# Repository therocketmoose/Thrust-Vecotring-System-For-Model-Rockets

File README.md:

Thrust Vectoring & Landing Control System for Model Rockets

Lead Engineer: Xavier Vimard
Project Start: 27/09/2025
Expected Completion: 20/05/2026

Project Overview:

This repository contains the full development of a thrust-controlled landing system (TCLS) for a model rocket platform. The project aims to design, build, and test a reusable model rocket capable of performing controlled ascent, attitude stabilization, descent management, and soft landing. The objective is to create a working proof-of-concept that integrates thrust vectoring, aerodynamic control, reaction wheel stabilization, and deployable landing legs into a unified flight system. This project is expected to operate over a one-year development window, with several intermediate prototypes and test campaigns.

The rocket platform itself is not the primary focus, the emphasis is the TCLS hardware, control algorithms, and validation testing necessary to achieve reliable vertical landing.

Project Goals:
- Develop a fully functional thrust vectoring system capable of four-axis gimbal control for ascent and landing.

- Implement a stability assist system using grid fins to manage minor deviations during ascent.

- Design a reaction wheel to counter roll and maintain thrust vector orientation.
as roll stabilization is critical, as uncontrolled roll makes TVC ineffective.

- Engineer deployable landing legs to ensure stable recovery after touchdown.

- Build a complete electronics and software stack integrating sensors, control logic, and closed-loop PID stabilization.

- Validate feasibility via simulation, static fire testing, and full-scale launch tests.

Development Timeline:

My project follows a structured month-by-month roadmap:

- Nov 2025: Design, print and stress test the TVC mount, the reaction wheel and the payload bay.
- Dec 2025: Design and simulate and prepare the code for the PCB.
- Jan 2026: Test the TVC with real motors, sssemble prototype rocket (without parachute), refine TVC mount, begin full system dry runs.
- Feb 2026: First flight test of the prototype, collect IMU/GPS data, evaluate control authority.
- Mar 2026: Analyze flight performance, improve PID tuning, begin landing system integration.
- Apr 2026: Integrate final landing mechanism, conduct ground validations.
- May 2026: Perform full integration test and finalize launch preparation for main flight.
- Jun 2026: Full-system launch and documentation of results.

System Architecture
Core Components:

- MCU: Teensy 4.1 — selected for deterministic real-time control performance.

- IMU: Bosch BMI088 — optimized for high-vibration flight profiles.

- Barometer: MS5611 — high-resolution altitude tracking (10 cm).

- Ground Sation: ESP32 and Lora reciever — supplementary system for communication and logging.

- Structure: Carbon fiber body, TVC gimbal, electronics bay, reaction wheel assembly.

CAD & Mechanical: 
The CAD design includes

- A 4-axis servo-driven TVC module.

- A compact reaction-wheel chamber below the nose cone.

- A payload bay positioned directly above the TVC to avoid cable latency.

Simulation Work

To validate feasibility, ascent and landing behavior is simulated using Xcos (SciLab).
Simulations include gyro stabilization behavior, ascent velocity and altitude curves, and TVC response testing. Early results indicate stable linear altitude growth and adequate thrust-to-weight margin, confirming the motor’s suitability for controlled ascent.

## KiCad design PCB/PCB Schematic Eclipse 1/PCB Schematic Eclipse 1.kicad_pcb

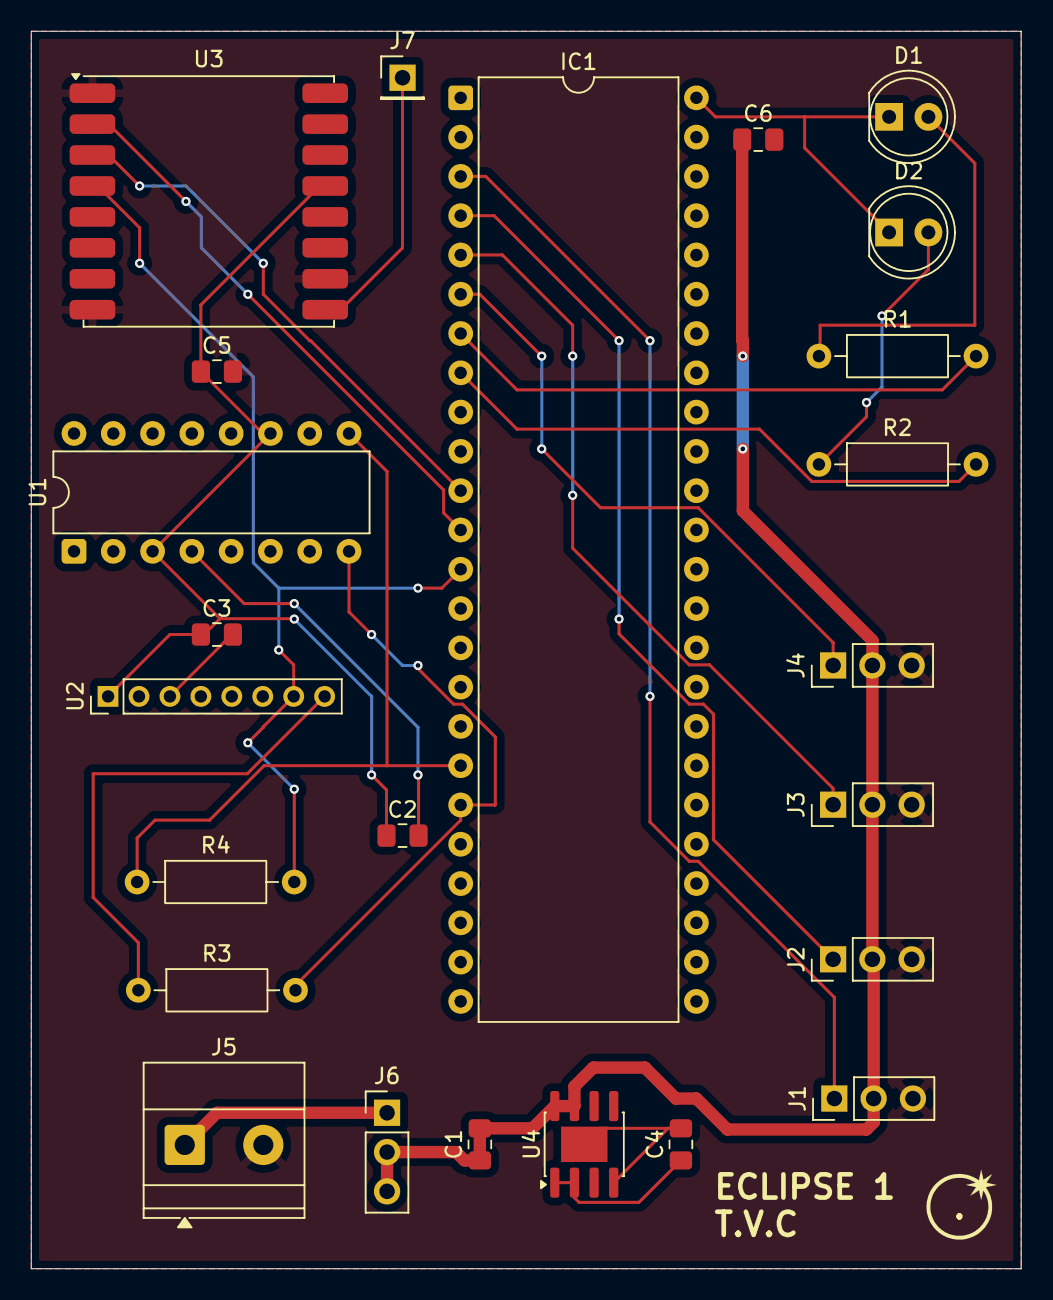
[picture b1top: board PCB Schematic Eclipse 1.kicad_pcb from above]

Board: 2 copper layers, 64.0 x 80.0 mm, 25 parts (0 on the bottom side), 24 nets.

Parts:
.: LOGO
C1, C4: C_Polarized; C_0805_2012Metric_Pad1.18x1.45mm_HandSolder
C2, C3, C5, C6: C; C_0805_2012Metric_Pad1.18x1.45mm_HandSolder
D1, D2: LED; LED_D5.0mm
IC1: TEENSY_4.1; DIP-48_W15.24mm
J1, J2, J3, J4, J6: Conn_01x03; PinHeader_1x03_P2.54mm_Vertical
J5: Conn_01x02_Pin; TerminalBlock_Phoenix_MKDS-1,5-2-5.08_1x02_P5.08mm_Horizont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
J7: Conn_01x01_Pin; PinHeader_1x01_P2.54mm_Vertical
R1, R2, R3, R4: R; R_Axial_DIN0207_L6.3mm_D2.5mm_P10.16mm_Horizontal
U1: BMI088; DIP-16_W7.62mm
U2: MS5611-01BA03; PinHeader_1x08_P2.00mm_Vertical
U3: RFM95W-868S2; HOPERF_RFM9XW_SMD
U4: ADP7142ARDZ-3.3; SOIC-8-1EP_3.9x4.9mm_P1.27mm_EP2.29x3mm

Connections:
/I2C_SCL: IC1.19 (A5), R3.2, U1.8 (SCL/SCK)
/I2C_SDA: IC1.18 (A4), R4.1, U1.9 (SDA/SDI)
/SPI_MISO: IC1.12 (MISO), U3.2 (MISO)
/SPI_MOSI: IC1.11 (MOSI), U3.3 (MOSI)
/SPI_SCK: IC1.13 (SCK), R4.2, U2.7 (SDI/SDA), U3.4 (SCK)
/VCC_3V3: C2.1, C3.1, C5.1, U1.3 (VDD), U1.11 (VDDIO), U2.1 (VDD), U3.13 (3_3V)
/Vcc_3V3: C4.1, U4.1 (VOUT), U4.2 (VOUT)
GND: C5.2, J1.3, J2.3, J3.3, J4.3, J5.2, U3.1 (GND), U3.8 (GND@1), U3.10 (GND@2)
unnamed: C4.2, U4.4 (GND), U4.9 (GND)
unnamed: D1.2 (A), R1.1
unnamed: D1.1 (K), D2.1 (K), IC1.48 (GND_2)
unnamed: D2.2 (A), R2.1
unnamed: IC1.4 (BCLK2), J2.1
unnamed: IC1.5 (IN2), J3.1
unnamed: IC1.3 (LRCLK2), J1.1
unnamed: IC1.6 (OUT1D), J4.1
unnamed: IC1.7 (RX2), R1.2
unnamed: IC1.8 (TX2), R2.2
unnamed: J5.1, J6.1
unnamed: J7.1, U3.9 (ANT)
unnamed: C2.2, U1.4 (GNDA)
unnamed: C3.2, U2.3 (GND)
unnamed: R3.1, U2.8 (SCLK)
VCC_5V: C1.1, C1.2, C6.1, J1.2, J2.2, J3.2, J4.2, J6.2, J6.3, U4.7 (VIN), U4.8 (VIN)

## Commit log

2025-12-04 Add final Pitch-Yaw control code including Kalman Filter files
2025-12-04 Rename Yaw__Pitch__Kalman_Filter_copy_20251107115251.ino to Kalman-Filter-Code.ino
2025-12-04 Rename Pitch-Yaw Control Code/Yaw__Pitch__Kalman_Filter_copy_20251107115251/Kalman-Filter-Code.ino to Yaw_Pitch_Kalman_Filter/Kalman-Filter-Code.ino
2025-12-05 Rename Xcos Simulations/.gitkeep to Simulations
2025-12-05 Create Simulations
2025-12-09 Full PCB
2025-12-09 Rename .gitkeep to .gitkeep
2025-12-09 Avionics Code
2025-12-09 Ground Station Code
2025-12-09 Update Yaw Pitch Code
2025-12-11 Rename Inner Gimbal.stl to Inner Gimbal.stl
2026-01-19 Changed stl files to step
2026-01-19 Create Full rocket cad (f3z)
2026-01-19 Create Full rocket CAD
2026-01-19 Revise README for clarity and updated visuals
    Updated image and clarified project focus in README.
2026-03-30 Replace old image with new screenshot
    Updated image in README.md to a new screenshot.
